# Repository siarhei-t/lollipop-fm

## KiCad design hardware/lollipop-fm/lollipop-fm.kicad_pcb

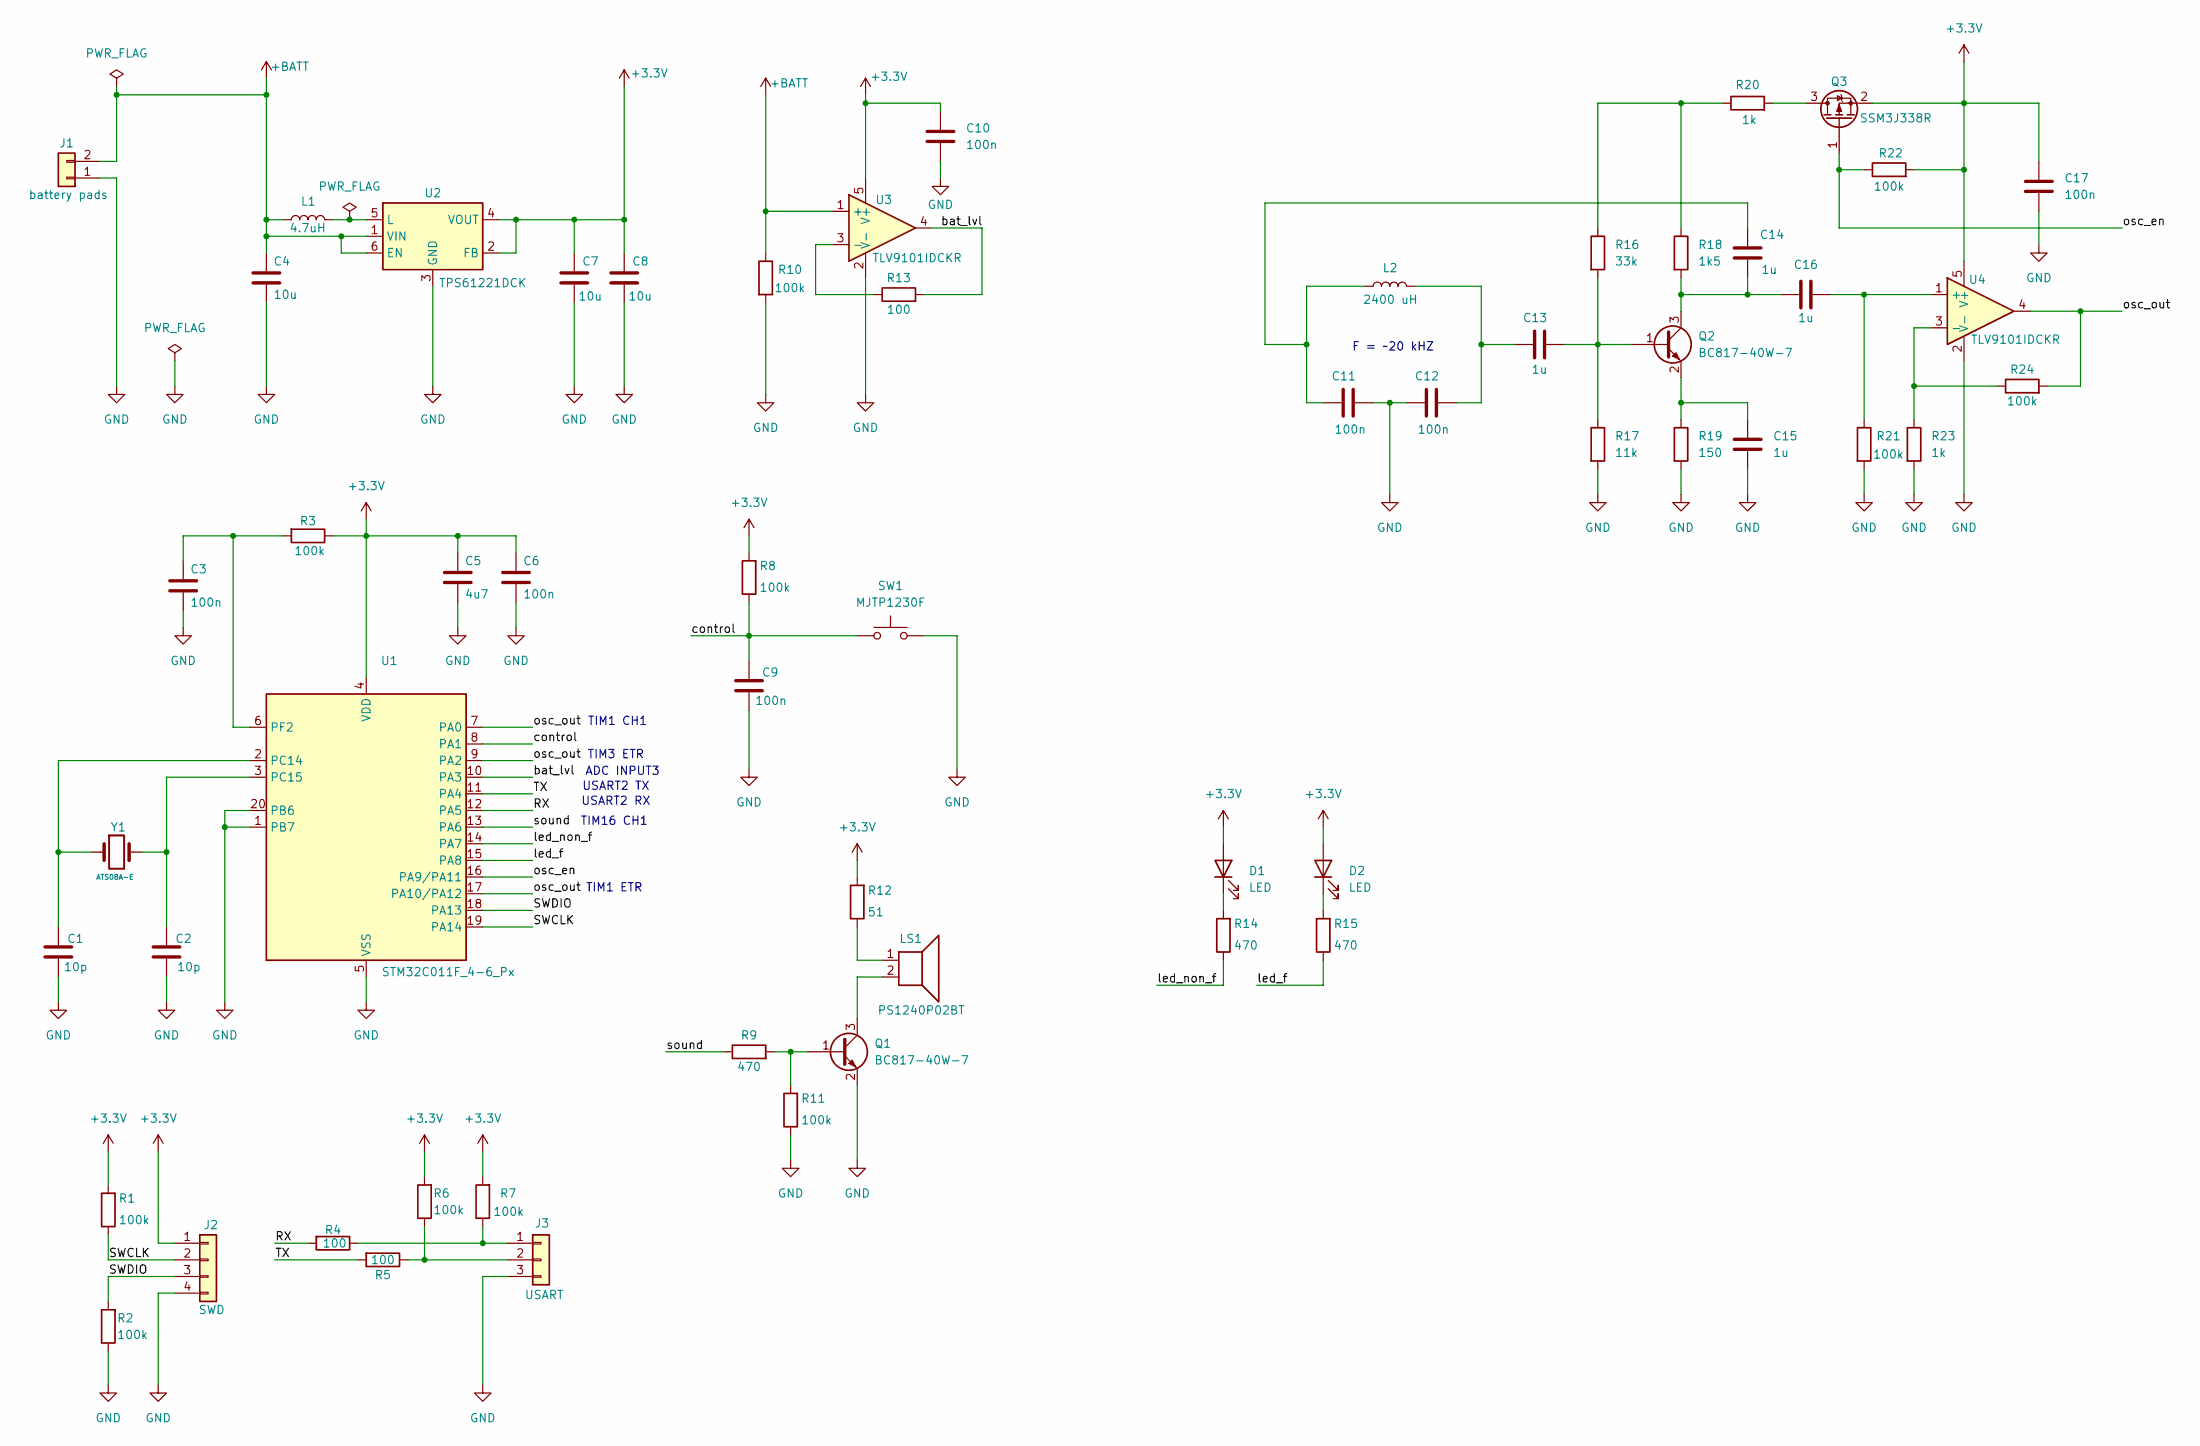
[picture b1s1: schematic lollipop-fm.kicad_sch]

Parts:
C1, C2: 10p; C_0603_1608Metric
C3, C6, C9, C10, C11, C12, C17: 100n; C_0603_1608Metric
C4, C7, C8: 10u; C_0603_1608Metric
C5: 4u7; C_0603_1608Metric
C13, C14, C15, C16: 1u; C_0603_1608Metric
D1, D2: LED; LED_D3.0mm
J1: battery pads; PinHeader_2x01_P2.54mm_Vertical
J2: SWD; pad-4-pin-2,54
J3: USART; pad-3-pin-2,54
L1: 4.7uH; L_0805_2012Metric
L2: 2400 uH; PinHeader_2x01_P2.54mm_Vertical
LS1: PS1240P02BT; Buzzer_12x9.5RM7.6
Q1, Q2: BC817-40W-7; SOT-323_SC-70_Handsoldering
Q3: SSM3J338R; SOT-23
R1, R2, R3, R6, R7, R8, R10, R11, R21, R22, R24: 100k; R_0603_1608Metric
R4, R5, R13: 100; R_0603_1608Metric
R9, R14, R15: 470; R_0603_1608Metric
R12: 51; R_0603_1608Metric
R16: 33k; R_0603_1608Metric
R17: 11k; R_0603_1608Metric
R18: 1k5; R_0603_1608Metric
R19: 150; R_0603_1608Metric
R20, R23: 1k; R_0603_1608Metric
SW1: MJTP1230F; SW_PUSH_6mm
U1: STM32C011F_4-6_Px; TSSOP-20_4.4x6.5mm_P0.65mm
U2: TPS61221DCK; Texas_R-PDSO-G6
U3, U4: TLV9101IDCKR; SOT-353_SC-70-5_Handsoldering
Y1: ATS08A-E; Crystal_HC49-4H_Vertical

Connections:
+3.3V: C5.1, C6.1, C7.2, C8.2, C10.1, C17.1, D1.2 (A), D2.2 (A), J2.1, Q3.2, R1.2, R3.1, R6.2, R7.2, R8.2, R12.2, R22.2, U1.4 (VDD), U2.2 (FB), U2.4 (VOUT), U3.5 (V+), U4.5 (V+)
+BATT: C4.1, J1.2, L1.1, R10.1, U2.1 (VIN), U2.6 (EN), U3.1 (+)
/RX: R4.2, U1.12 (PA5)
/SWCLK: J2.2, R1.1, U1.19 (PA14)
/SWDIO: J2.3, R2.2, U1.18 (PA13)
/TX: R5.2, U1.11 (PA4)
/bat_lvl: R13.2, U1.10 (PA3), U3.4
/control: C9.2, R8.1, SW1.1, U1.8 (PA1)
/led_f: R15.1, U1.15 (PA8)
/led_non_f: R14.1, U1.14 (PA7)
/osc_en: Q3.1, R22.1, U1.16 (PA9/PA11)
/osc_out: R24.2, U1.7 (PA0), U1.9 (PA2), U1.17 (PA10/PA12), U4.4
/sound: R9.1, U1.13 (PA6)
GND: C1.2, C2.2, C3.2, C4.2, C5.2, C6.2, C7.1, C8.1, C9.1, C10.2, C11.2, C12.1, C15.2, C17.2, J1.1, J2.4, J3.3, Q1.2 (E), R2.1, R10.2, R11.1, R17.2, R19.2, R21.2, R23.2, SW1.2, U1.1 (PB7), U1.5 (VSS), U1.20 (PB6), U2.3 (GND), U3.2 (V-), U4.2 (V-)
unnamed: C11.1, C14.1, L2.1
unnamed: C12.2, C13.1, L2.2
unnamed: D1.1 (K), R14.2
unnamed: D2.1 (K), R15.2
unnamed: J3.1, R4.1, R7.1
unnamed: J3.2, R5.1, R6.1
unnamed: LS1.1, R12.1
unnamed: Q1.1 (B), R9.2, R11.2
unnamed: LS1.2, Q1.3 (C)
unnamed: C13.2, Q2.1 (B), R16.2, R17.1
unnamed: C14.2, C16.1, Q2.3 (C), R18.2
unnamed: C15.1, Q2.2 (E), R19.1
unnamed: Q3.3, R20.2
unnamed: R16.1, R18.1, R20.1
unnamed: C1.1, U1.2 (PC14), Y1.1
unnamed: C2.1, U1.3 (PC15), Y1.2
unnamed: C3.1, R3.2, U1.6 (PF2)
unnamed: L1.2, U2.5 (L)
unnamed: R13.1, U3.3 (-)
unnamed: C16.2, R21.1, U4.1 (+)
unnamed: R23.1, R24.1, U4.3 (-)

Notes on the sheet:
ADC INPUT3
TIM1 CH1
USART2 TX
F = ~20 kHZ
USART2 RX
TIM1 ETR
TIM16 CH1
TIM3 ETR

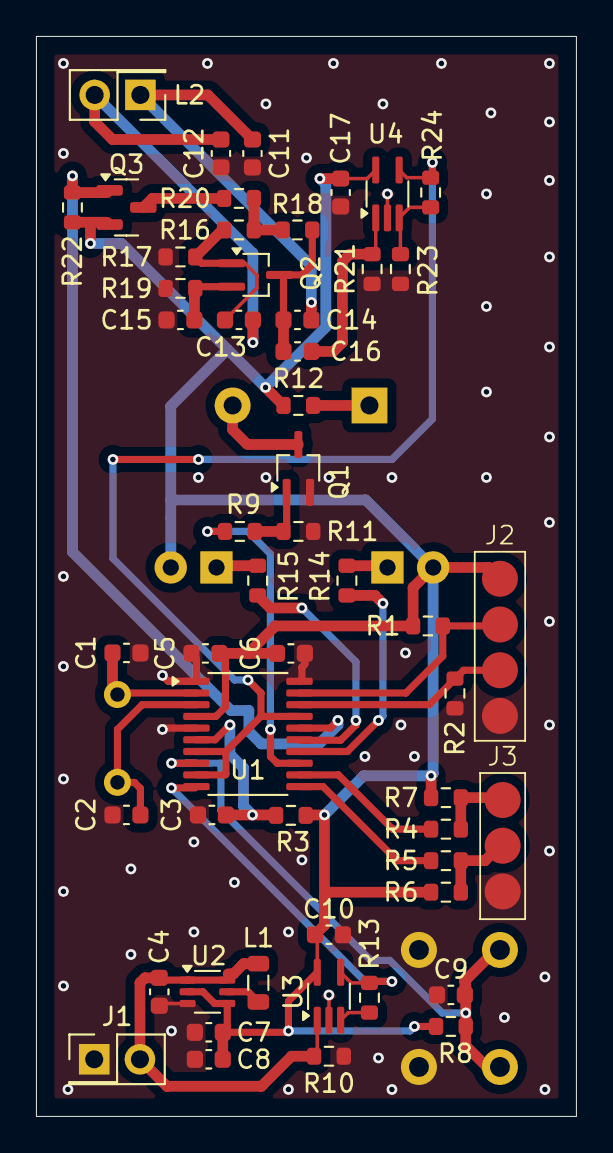
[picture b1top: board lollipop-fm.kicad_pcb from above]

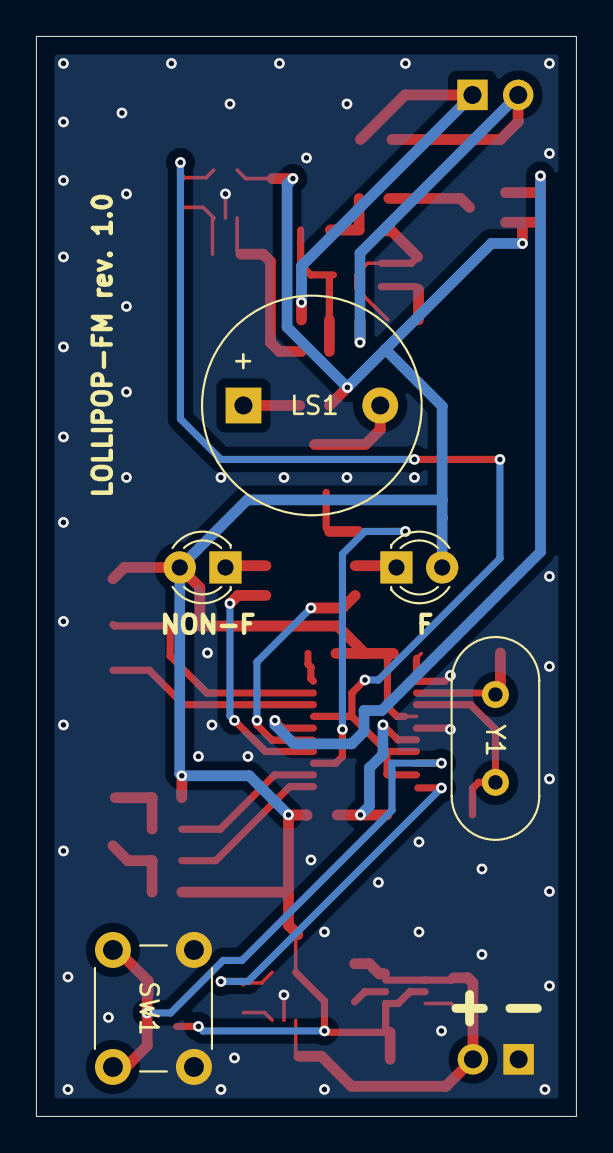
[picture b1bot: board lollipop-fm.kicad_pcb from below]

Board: 2 copper layers, 30.0 x 60.0 mm, 58 parts (5 on the bottom side), 35 nets.

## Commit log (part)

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2025-12-29 - added CMSIS device support and linker script for stm32c011
2025-12-29 - added common Cmake file and system init
2025-12-30 - added vscode project, tasks and minimal build
2025-12-31 - added .gitignore
2025-12-31 - added FreeRTOS kernel as submodule
2025-12-31 - added build for FreeRTOS to test build possibility
2026-01-01 - syscalls added, added debug config for vscode, build tested
2026-01-01 - build switched to C++ application
2026-01-02 - added led control, added first FreeRTOS task for led control
2026-01-03 - led control switched to static task logic
2026-01-03 - doxygen updated, blink task updated
2026-01-04 - added class for serial port output
2026-01-04 - added main task, console print tested
2026-01-07 - RTOS stack usage fixed
2026-01-07 - system switched to internal clock
2026-01-07 - hardware tested, first version of colpitts oscillator works
2026-01-08 - added separated class for gpio control
2026-01-09 - added calibration request on button press event
2026-01-09 - manual calibration tested
2026-01-09 - added empty files for buzzer control
2026-01-10 - buzzer tested
2026-01-18 - added external configuration file
2026-01-18 - added empty buzzer task
2026-01-18 - added draft for sound play logic
2026-01-19 - buzzer to be fixed for one tone usage, led will be only one
2026-02-01 - added empty hardware project
2026-03-15 - imported old schematic
2026-03-15 - schematic updated with latest changes
2026-03-16 - new routing added
2026-03-17 - production files generated
2026-04-18 - gitignore updated, added sublime text project file
2026-04-19 - led control logic updated, schematic naming updated
2026-04-19 - clangd for sublime text fixed
2026-04-26 - buzzer logic refactored
2026-04-26 - I/O logic refactored
2026-04-26 - serial port logic refactored
2026-05-16 - frequency meter logic refactored
2026-05-16 - old comments removed
2026-05-23 - added debug flags for CXX files
2026-05-23 - new board tested
2026-05-23 - to be switched to the old buzzer
2026-05-24 - TEST
2026-05-24 - new fm alg updated
2026-05-24 - buzzer logic updated
2026-05-24 - WIP, schematic tested
2026-05-24 - calibration function updated
2026-06-14 - logic updated, added simple filter with drift tracking
